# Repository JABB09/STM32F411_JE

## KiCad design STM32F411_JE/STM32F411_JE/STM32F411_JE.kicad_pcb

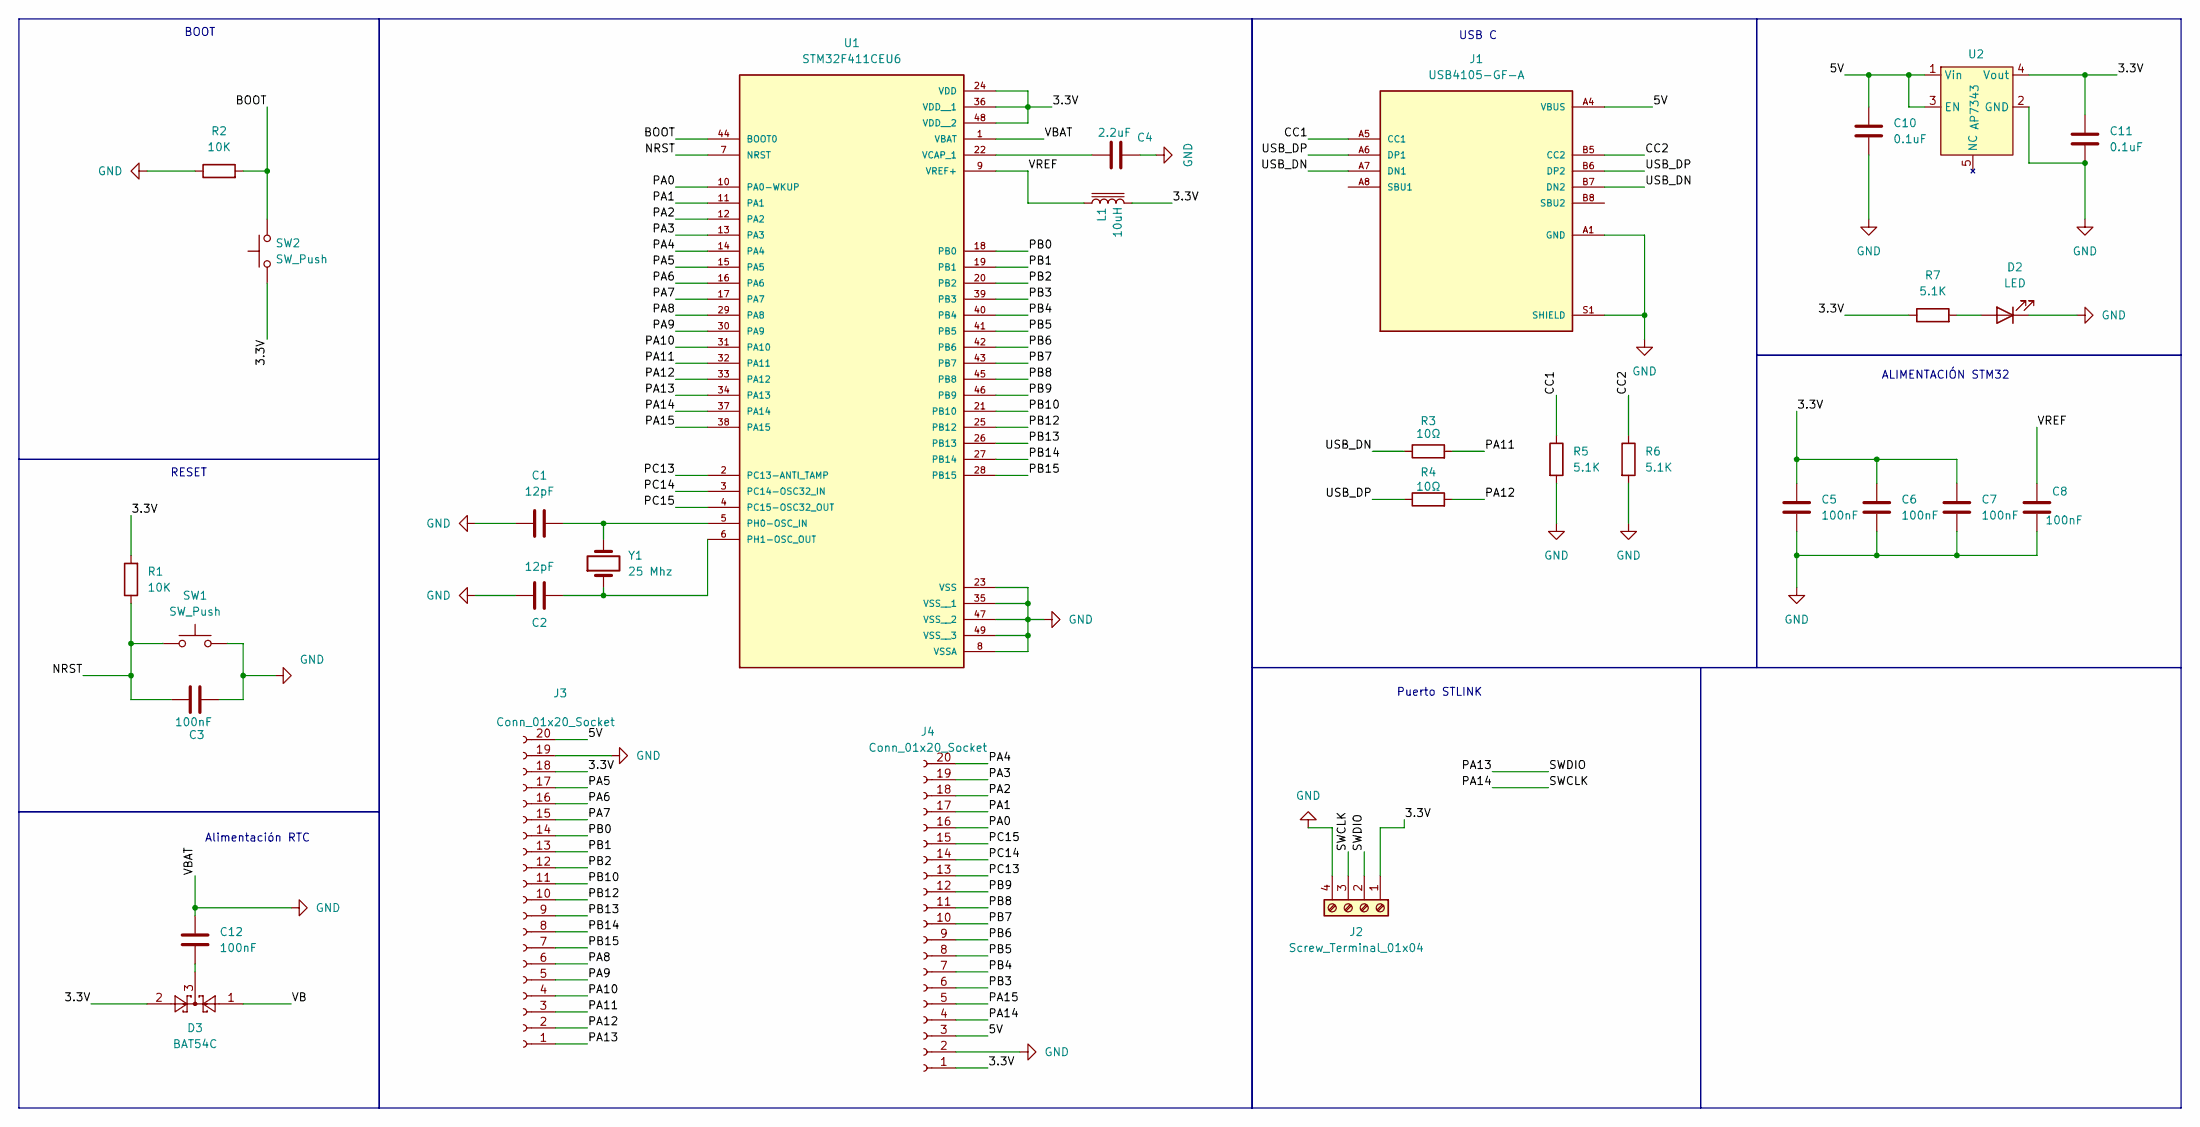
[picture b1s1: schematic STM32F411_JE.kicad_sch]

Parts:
C1, C2: 12pF; C_0603_1608Metric_Pad1.08x0.95mm_HandSolder
C3, C5, C6, C7, C8, C12: 100nF; C_0603_1608Metric_Pad1.08x0.95mm_HandSolder
C4: 2.2uF; C_0603_1608Metric_Pad1.08x0.95mm_HandSolder
C10, C11: 0.1uF; C_0603_1608Metric_Pad1.08x0.95mm_HandSolder
D2: LED; LED_0603_1608Metric
D3: BAT54C; SOT-23
J1: USB4105-GF-A; GCT_USB4105-GF-A; PARTREV B4
J2: Screw_Terminal_01x04; PinHeader_1x04_P2.54mm_Horizontal
J3, J4: Conn_01x20_Socket; PinHeader_1x20_P2.54mm_Vertical
L1: 10uH; L_0603_1608Metric
R1, R2: 10K; R_0603_1608Metric_Pad0.98x0.95mm_HandSolder
R3, R4: 10Ω; R_0603_1608Metric_Pad0.98x0.95mm_HandSolder
R5, R6: 5.1K; R_0805_2012Metric
R7: 5.1K; R_0603_1608Metric_Pad0.98x0.95mm_HandSolder
SW1, SW2: SW_Push; SW_SPST_CK_RS282G05A3
U1: STM32F411CEU6; QFN50P700X700X60-49N; PARTREV 7
U2: AP7343; SOT-23-5
Y1: 25 Mhz; Crystal_SMD_0603-2Pin_6.0x3.5mm

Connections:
/3.3V: C5.1, C6.1, C7.1, C11.1, D3.2, J2.1, J3.18, J4.1, L1.2, R1.2, R7.1, SW2.1, U1.24 (VDD), U1.36 (VDD__1), U1.48 (VDD__2), U2.4 (Vout); also elsewhere on the board
/5V: C10.1, J1.A4 (VBUS), J3.20, J4.3, U2.1 (Vin), U2.3 (EN)
/BOOT: R2.2, SW2.2, U1.44 (BOOT0); also elsewhere on the board
/CC1: J1.A5 (CC1), R5.1
/CC2: J1.B5 (CC2), R6.1
/NRST: C3.1, R1.1, SW1.1, U1.7 (NRST); also elsewhere on the board
/PA0: J4.16, U1.10 (PA0-WKUP)
/PA1: J4.17, U1.11 (PA1)
/PA2: J4.18, U1.12 (PA2)
/PA3: J4.19, U1.13 (PA3)
/PA4: J4.20, U1.14 (PA4)
/PA5: J3.17, U1.15 (PA5)
/PA6: J3.16, U1.16 (PA6)
/PA7: J3.15, U1.17 (PA7)
/PA8: J3.6, U1.29 (PA8)
/PA9: J3.5, U1.30 (PA9)
/PA10: J3.4, U1.31 (PA10)
/PA11: J3.3, R3.2, U1.32 (PA11)
/PA12: J3.2, R4.2, U1.33 (PA12)
/PA13: J2.2, J3.1, U1.34 (PA13)
/PA14: J2.3, J4.4, U1.37 (PA14)
/PA15: J4.5, U1.38 (PA15)
/PB0: J3.14, U1.18 (PB0)
/PB1: J3.13, U1.19 (PB1)
/PB2: J3.12, U1.20 (PB2)
/PB3: J4.6, U1.39 (PB3)
/PB4: J4.7, U1.40 (PB4)
/PB5: J4.8, U1.41 (PB5)
/PB6: J4.9, U1.42 (PB6)
/PB7: J4.10, U1.43 (PB7)
/PB8: J4.11, U1.45 (PB8)
/PB9: J4.12, U1.46 (PB9)
/PB10: J3.11, U1.21 (PB10)
/PB12: J3.10, U1.25 (PB12)
/PB13: J3.9, U1.26 (PB13)
/PB14: J3.8, U1.27 (PB14)
/PB15: J3.7, U1.28 (PB15)
/PC13: J4.13, U1.2 (PC13-ANTI_TAMP)
/PC14: J4.14, U1.3 (PC14-OSC32_IN)
/PC15: J4.15, U1.4 (PC15-OSC32_OUT)
/USB_DN: J1.A7 (DN1), J1.B7 (DN2), R3.1
/USB_DP: J1.A6 (DP1), J1.B6 (DP2), R4.1
/VB: D3.1
/VREF: C8.1, L1.1, U1.9 (VREF+)
GND: C1.1, C2.1, C3.2, C4.1, C5.2, C6.2, C7.2, C8.2, C10.2, C11.2, C12.1, D2.1 (K), J1.A1 (GND), J1.S1 (SHIELD), J2.4, J3.19, J4.2, R2.1, R5.2, R6.2, SW1.2, U1.1 (VBAT), U1.8 (VSSA), U1.23 (VSS), U1.35 (VSS__1), U1.47 (VSS__2), U1.49 (VSS__3), U2.2 (GND); also elsewhere on the board
unnamed: C12.2, D3.3
unnamed: D2.2 (A), R7.2
unnamed: C1.2, U1.5 (PH0-OSC_IN), Y1.2
unnamed: C2.2, U1.6 (PH1-OSC_OUT), Y1.1
unnamed: C4.2, U1.22 (VCAP_1)

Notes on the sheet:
Alimentación RTC
RESET
Puerto STLINK
BOOT
ALIMENTACIÓN STM32
USB C

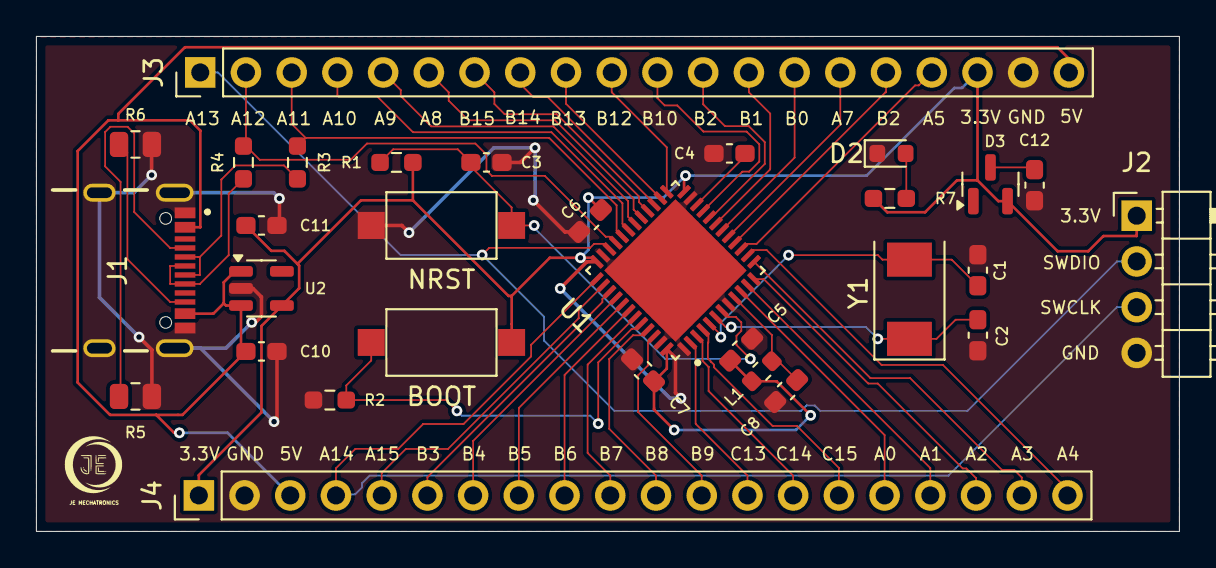
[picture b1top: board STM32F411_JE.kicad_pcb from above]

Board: 2 copper layers, 63.5 x 27.5 mm, 30 parts (0 on the bottom side), 49 nets.

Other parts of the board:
BOOT: SW_Push; SW_SPST_CK_RS282G05A3
NRST: SW_Push; SW_SPST_CK_RS282G05A3

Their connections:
/3.3V: BOOT.1; also elsewhere on the board
/BOOT: BOOT.2; also elsewhere on the board
/NRST: NRST.1; also elsewhere on the board
GND: NRST.2; also elsewhere on the board

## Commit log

2024-08-26 Commit inicial
2024-08-26 Se agrega microcontrolador stm32 al plano
2024-08-27 Se agrega el circuito de boot, de alimentación, de reset, y alimentación del rtc
2024-08-27 Recuperación proyecto
2024-08-27 Se actualiza el simbolo del usb tipo c del submodulo
2024-08-27 Se actualiza libreria usb tipo c
2024-08-27 Se actualiza biblioteca de simbolos
2024-08-27 Se termina el diseño esquematico de el STM32F411_JE
2024-08-27 Se agrega footprint a stm32
2024-08-27 revision de pines
2024-08-27 Se agrega archivo .lck al .gitignore
2024-08-27 Actualización del submódulo a commit 4383b5d
2024-08-27 actualizacion de archivos
2024-08-27 intento fallido de pcb
2024-08-27 commit modificaciones librerias
2024-08-28 Se agregan etiquetas de los pines al diseño de la PCB
2024-08-28 diseño pcb
2024-08-28 Prueba actualizacion
2024-08-28 Se agrega la carpeta de imagenes
2024-08-28 actualizacion librerias
2024-08-28 Actualizacion libreria
2024-08-28 Se termina el diseño de la zona de cobre de la pcb
2024-08-28 resolviendo mi cagada
2024-08-28 Actualización biblioteca
2024-08-28 julian el mas bonito
2024-08-28 se añadio logo
2024-08-28 fixing
